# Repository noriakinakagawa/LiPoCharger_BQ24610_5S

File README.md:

# LiPoCharger_BQ24610_5S
パワーパス付きのリチウムポリマーバッテリ5セルの充電基板です。分圧抵抗値を変えることで電流や電圧を変えられます。

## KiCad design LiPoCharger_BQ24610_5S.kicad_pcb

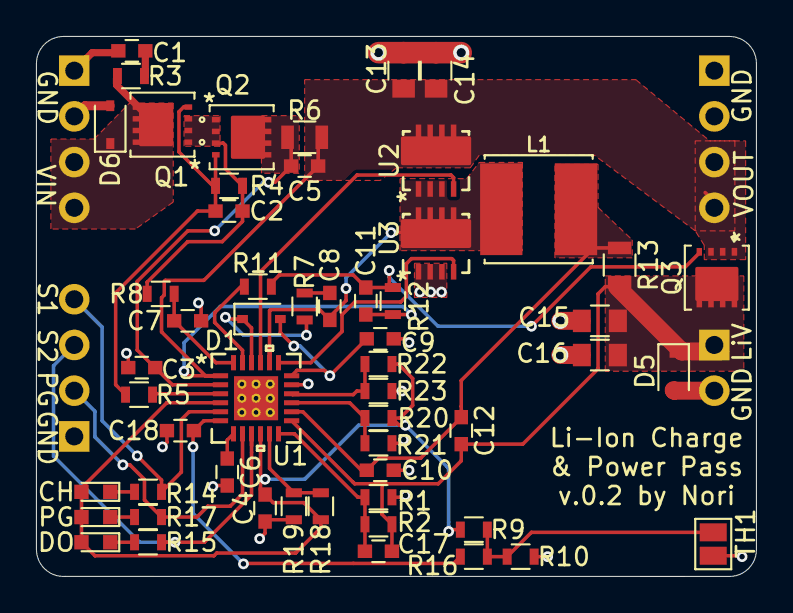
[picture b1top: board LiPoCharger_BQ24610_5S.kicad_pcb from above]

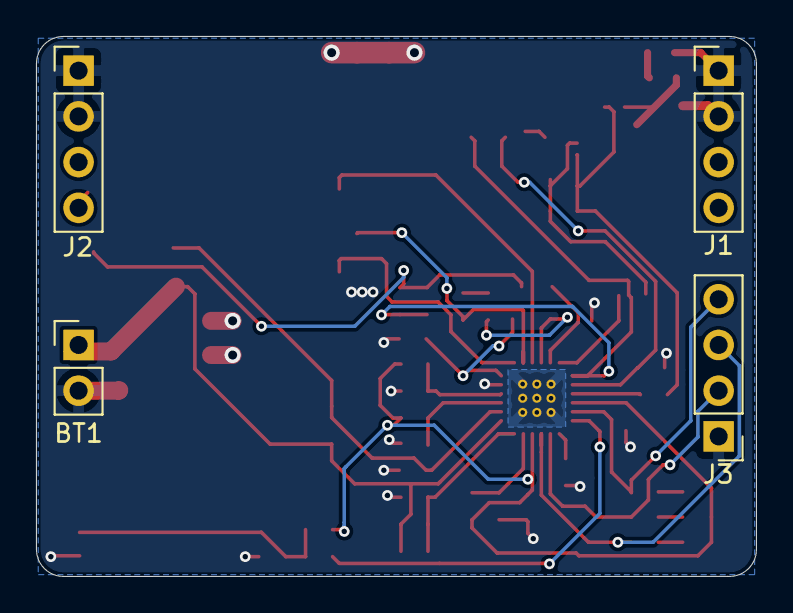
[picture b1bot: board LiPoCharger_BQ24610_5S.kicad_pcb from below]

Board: 2 copper layers, 40.0 x 30.0 mm, 59 parts (4 on the bottom side), 33 nets.

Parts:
BT1: LiPo_5S; Pin_Header_Straight_1x02_Pitch2.54mm
C1, C7, C9: 1u; C_0603
C2, C3, C4, C5, C6, C8, C10, C11, C12, C18: 0.1u; C_0603
C13, C14, C15, C16: 10u; C_0805
C17: 22p; C_0603
CH: LED; LED_0603
D1: CUS520,H3F; D_SOD-323
D5, D6: D_Zener; D_SOD-323
DO: LED; LED_0603
J1, J2, J3: Conn_01x04; Pin_Header_Straight_1x04_Pitch2.54mm
L1: 6.8u3.5A; IND_SRN6045TA-3R3Y
PG: LED; LED_0603
Q1, Q2, Q3: SISH101DN-T1-GE3; SISH625DN-T1-GE3
R1: 130k 1%; R_0603
R2: 1.1M 1%; R_0603
R3, R8: 10; R_0603
R4, R12, R23: 100k; R_0603
R5, R11: 1k; R_0603
R6, R13: 10m; R_0805
R7: 0; R_0603
R9: 9.31k 1%; R_0603
R10: 430k 1%; R_0603
R14, R15, R17: 10k; R_0603
R16: 100; R_0603
R18: 510k; R_0603
R19: 33k; R_0603
R20: 240k; R_0603
R21: 7.5k; R_0603
R22: 560k; R_0603
TH1: RTH103AT; SolderJumper-2_P1.3mm_Open_Pad1.0x1.5mm
U1: BQ24610RGER
U2, U3: TPN2R304PL; TPN1R603PL

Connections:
+BATT: BT1.1, C12.2, C15.1, C16.1, C17.1, D5.1, Q3.5, Q3.6, Q3.7, Q3.8, R2.1, R13.1, U1.13
ACSET: R22.2, R23.1, U1.16
GND: BT1.2, C1.2, C3.1, C4.2, C6.2, C7.2, C9.2, C10.2, C13.2, C14.2, C15.2, C16.2, C18.2, D5.2, D6.2, J1.1, J1.2, J2.1, J2.2, J3.1, R1.2, R10.2, R19.2, R21.2, R23.2, TH1.2, U1.17, U1.25, U3.1, U3.2, U3.3
ISET1: R18.2, R19.1, U1.11
ISET2: R20.2, R21.1, U1.15
unnamed: C1.1, R3.1
unnamed: C2.1, Q1.1, Q1.2, Q1.3, Q2.1, Q2.2, Q2.3, R4.2, R8.2
unnamed: C2.2, Q1.4, Q2.4, R4.1, R5.1
unnamed: C3.2, C5.1, Q2.5, Q2.6, Q2.7, Q2.8, R6.2, U1.2
unnamed: C6.1, U1.7
unnamed: C7.1, R8.1, U1.24
unnamed: C8.1, R7.1
unnamed: C8.2, L1.1, U1.20, U2.1, U2.2, U2.3, U3.5, U3.6, U3.7, U3.8
unnamed: C9.1, D1.2, U1.18
unnamed: C10.1, C12.1, L1.2, R13.2, U1.14
unnamed: C5.2, C11.1, C13.1, C14.1, J2.3, J2.4, Q3.1, Q3.2, Q3.3, R6.1, R12.2, U1.1, U2.5, U2.6, U2.7, U2.8
unnamed: C11.2, Q3.4, R11.2, R12.1
unnamed: D1.1, R7.2, U1.22
unnamed: CH.1, R14.1
unnamed: DO.1, R15.1
unnamed: PG.1, R17.1
unnamed: D6.1, J1.3, J1.4, Q1.5, Q1.6, Q1.7, Q1.8, R3.2
unnamed: R5.2, U1.3
unnamed: R9.2, R10.1, R16.2, TH1.1
unnamed: R11.1, U1.23
unnamed: U1.19, U3.4
unnamed: U1.21, U2.4
STAT1: J3.4, R14.2, U1.5
STAT2: J3.3, R15.2, U1.9
TS: C18.1, R16.1, U1.6
VFB: C17.2, R1.1, R2.2, U1.12
VREF: C4.1, CH.2, DO.2, PG.2, R9.1, R18.1, R20.1, R22.1, U1.4, U1.10
~PG: J3.2, R17.2, U1.8

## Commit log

2021-11-27 Modification
    Added Zener diode 27V on the power input side.
